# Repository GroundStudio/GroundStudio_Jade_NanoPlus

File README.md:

GroundStudio Jade Nano+
====================================

Get it from [ardushop.ro](https://ardushop.ro/ro/home/2500-jade-nano.html)

Explore all the GroundStudio products at [GroundStudio.ro](https://groundstudio.ro/)

Description
-------------------
ATMEGA328PB based development board featuring picoPower® technology for better power management, Peripheral Touch Controller (PTC), 32kBytes of In-System Self-Programmable Flash program memory,  1kBytes EEPROM, 2kBytes Internal SRAM, 9 PWM Channels, 22 Digital Pins, 2 USART, 2 SPI, I²C  and 8 channel 10 bit ADC Pins and HT42B534-2 for USB comunication.

Contents
-------------------

* [/Documentation](https://github.com/GroundStudio/GroundStudio_Jade_NanoPlus/tree/main/Documentation/) -- Pinout.
* [/Hardware](https://github.com/GroundStudio/GroundStudio_Jade_NanoPlus/tree/main/Hardware/) -- Schematics, layout.

Versions
-------------------
*(Not all tags shown)*
- [REV0.0.2]:
  - removed R11 and R12

License
-------------------

This is released under the [Attribution-ShareAlike 4.0 International (CC BY-SA 4.0)](https://creativecommons.org/licenses/by-sa/4.0/) license. 
**You are welcome to use this for commercial purposes.**

Please consider contributing back to this project or others to help the open-source hardware community continue to thrive and grow!

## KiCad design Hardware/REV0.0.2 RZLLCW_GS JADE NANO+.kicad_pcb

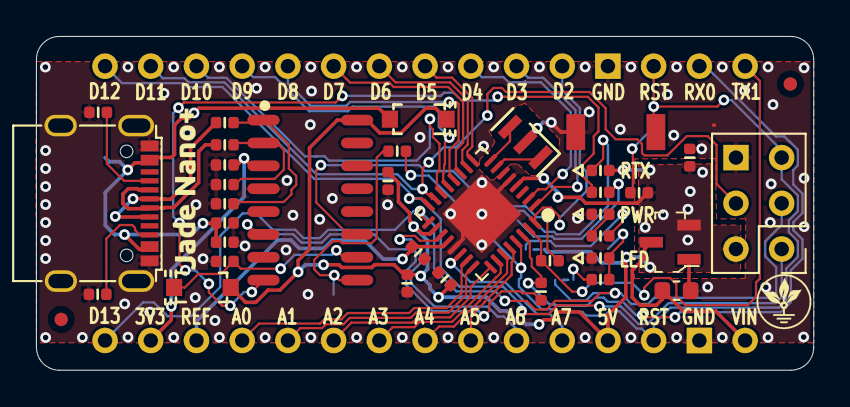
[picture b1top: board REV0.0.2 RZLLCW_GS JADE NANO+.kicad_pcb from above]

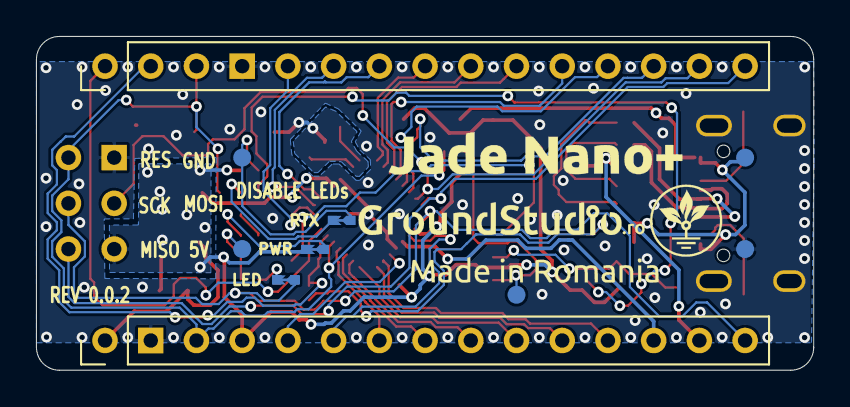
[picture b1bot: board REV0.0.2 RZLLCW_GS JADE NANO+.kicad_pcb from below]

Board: 2 copper layers, 43.2 x 18.5 mm, 47 parts (5 on the bottom side), 48 nets.

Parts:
C1: C_0402_1uF_10V; C_0402_alt
C2, C3, C4, C7, C9, C11: C_0402_100nF_16V; C_0402_alt
C5: C_0603_1uF_50V; C_0603
C6, C8, C10: C_0402_4.7uF_16V; C_0402_alt
C12, C13: C_0402_47pF_50V; C_0402_alt
D1: LED_0402_RED; LED_0402_alt
D2, D4: SOD-123 B0520LW; SOD-123
D3: LED_0402_GREEN; LED_0402_alt
FID1, FID2: Fiducial; Fiducial_0.75mm_Mask1.5mm
IC1: SOP-16_150MIL HT42B534-2; SOP-16_150MIL
J1, J2: PinHeader_1x15_P2.54_V_M B-2100S15P-A110; PinHeader_1x15_P2.54mm_Vertical_Male
J3: PinHeader_2x03_P2.54_V_M 210-72-03GB01; PinHeader_2x03_P2.54mm_Vertical_Male
J4: L LED DISABLE; SolderJumper_NC_small
J5: RTX LED DISABLE; SolderJumper_NC_small
J6: PWR LED DISABLE; SolderJumper_NC_small
LED_POW1: LED_0402_RED; LED_0402_alt
R1, R2: R_0402_1k; R_0402_alt
R3, R6, R7: R_0402_20k; R_0402_alt
R4: R_0402_10k; R_0402_alt
R5, R8: R_0402_33; R_0402_alt
R9, R10: R_0402_5.1k; R_0402_alt
SW1: TS342A2P-WZ
TP1: TestPoint RxTx; TestPoint
TP_DTR2: TestPoint
TP_LL1: TestPoint
TP_USH1: TestPoint
TP_VBUS1: TestPoint
U1: QFN-32-1EP_5x5_P0.5_328PB-MN; QFN-32-1EP_5x5mm_P0.5mm_EP3.1x3.1mm
U3: SOT-23-3 SSP7603P50MR; SOT-23-3
USB1: USB_C 918-418K2023S40001; USB_C_C167321
Y1: Resonator_3Pin_3.2x1.3 CSTNE16M0V; CSTNE

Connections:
+3V3: C1.1, IC1.3, J2.14
+5V: C2.2, C6.1, C7.1, C8.1, D1.2, D2.2, D4.1, IC1.16, J2.4, J3.2, J6.2, R4.2, U1.4, U1.18, U3.2
/UD+: C13.1, IC1.1, R5.1
/UD-: C12.2, IC1.2, R8.2
A0: J2.12, U1.23
A1: J2.11, U1.24
A2: J2.10, U1.25
A3: J2.9, U1.26
A4: J2.8, U1.27
A5: J2.7, U1.28
A6: J2.6, U1.19
A7: J2.5, U1.22
AREF: C4.1, J2.13, U1.20
D0-uC_RX: J1.2, R1.2, U1.30
D1-uC_TX: J1.1, R2.2, U1.31
D2: J1.5, U1.32
D3: J1.6, U1.1
D4: J1.7, U1.2
D5: J1.8, U1.9
D6: J1.9, U1.10
D7: J1.10, U1.11
D8: J1.11, U1.12
D9: J1.12, U1.13
D10: J1.13, U1.14
D11-MOSI: J1.14, J3.4, U1.15
D12-MISO: J1.15, J3.1, U1.16
D13-SCK: J2.15, J3.3, J4.1, U1.17
D+: R5.2, USB1.A6, USB1.B6
D-: R8.1, USB1.A7, USB1.B7
GND: C1.2, C2.1, C3.1, C4.2, C5.2, C6.2, C7.2, C8.2, C10.2, C11.2, C12.1, C13.2, D3.1, IC1.4, J1.4, J2.2, J3.6, LED_POW1.1, R9.1, R10.2, SW1.1, TP_USH1.~, U1.5, U1.21, U1.33, U3.1, USB1.0, USB1.A1, USB1.A12, USB1.B1, USB1.B12, Y1.2
HOLTEK_RX: IC1.11, R2.1
HOLTEK_TX: IC1.6, R1.1
unnamed: C3.2, D2.1, IC1.10
unnamed: C9.2, IC1.9, TP_DTR2.~
unnamed: D1.1, J5.1, TP1.~
unnamed: D3.2, R7.2, TP_LL1.~
unnamed: IC1.8, R3.1
unnamed: J4.2, R7.1
unnamed: J5.2, R3.2
unnamed: J6.1, R6.2
unnamed: LED_POW1.2, R6.1
unnamed: R9.2, USB1.B5
unnamed: R10.1, USB1.A5
VIN: C5.1, J2.1, U3.3
VUSB: C10.1, C11.1, D4.2, TP_VBUS1.~, USB1.A4, USB1.A9, USB1.B4, USB1.B9
XTAL1: U1.7, Y1.1
XTAL2: U1.8, Y1.3
uC_Reset: C9.1, J1.3, J2.3, J3.5, R4.1, SW1.2, U1.29

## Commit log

2022-08-04 - initial commit
2022-08-04 - better organisation
2022-08-05 - pinout credits update
2022-08-05 - board name fix
2022-08-11 - better pinout graphics
2022-08-26 - added schematic pdf file
2022-08-26 - added "Kicad6" to revision folder name
2023-03-15 Update README.md
    - removed references to "library"
